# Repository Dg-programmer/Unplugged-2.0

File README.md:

# Unplugged-2.0
Round 2 Codes &amp; Snippets

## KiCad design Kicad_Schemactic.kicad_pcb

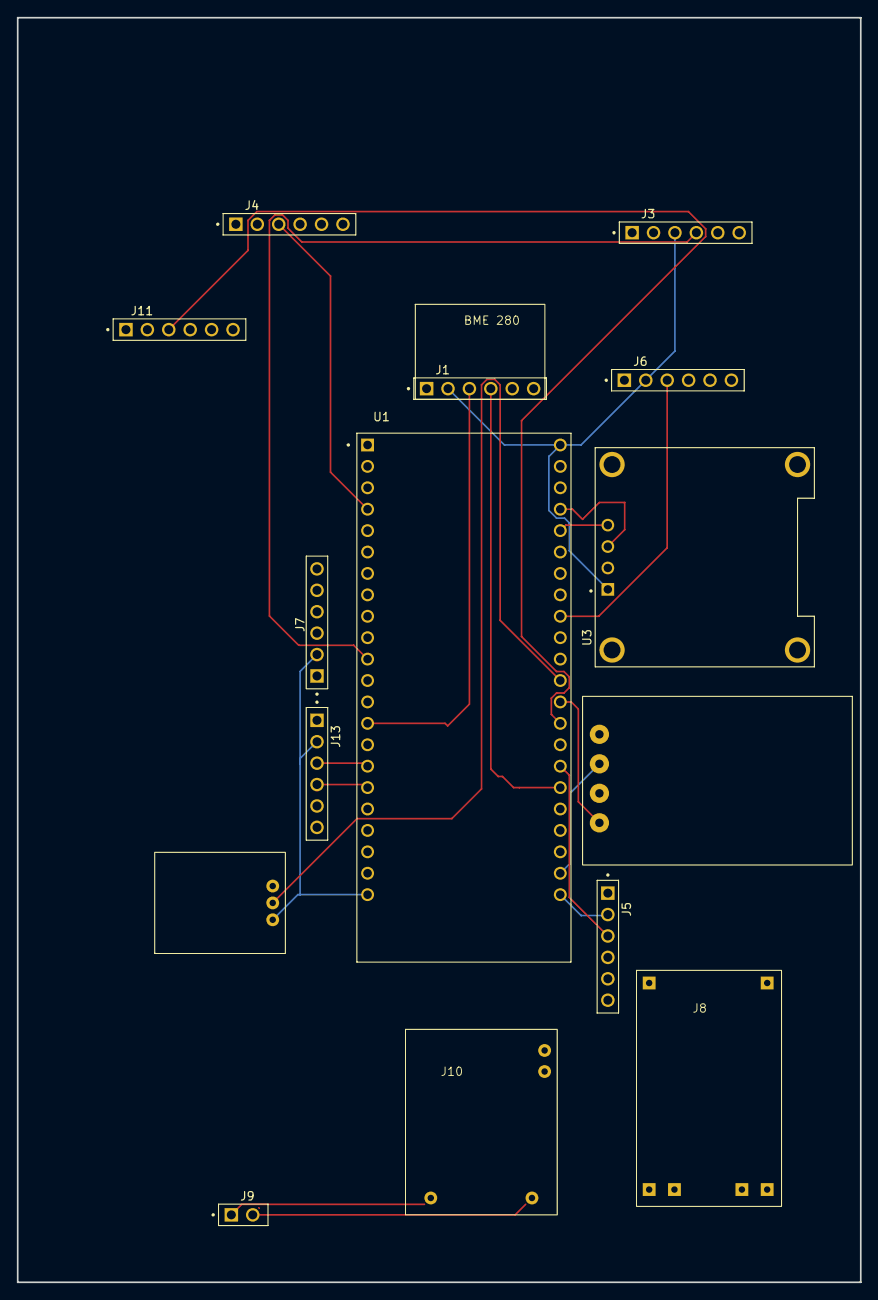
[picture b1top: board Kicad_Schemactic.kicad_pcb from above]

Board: 2 copper layers, 100.0 x 150.0 mm, 15 parts (0 on the bottom side), 16 nets.

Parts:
J1: BME 280; SULLINS_PPTC061LFBN-RC
J2: MQ 135; MQ 185
J3: PMY 2.5; SULLINS_PPTC061LFBN-RC
J4: water sensor; SULLINS_PPTC061LFBN-RC
J5, J7: IR sensor; SULLINS_PPTC061LFBN-RC
J6: Sound Sensor; SULLINS_PPTC061LFBN-RC
J8: Tp4056; TP4056
J9: Battery; SULLINS_PPTC061LFBN-RC
J10: BOOST; Boost
J11: Hall effect; SULLINS_PPTC061LFBN-RC
J12: DHT11
J13: RTC; SULLINS_PPTC061LFBN-RC
U1: ESP32-S3-DEVKITC-1U-N8R2; XCVR_ESP32-S3-DEVKITC-1U-N8R2
U3: Oled display; MODULE_DM-OLED096-636

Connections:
3v: J1.1 (VCC), J2.1 (VCC), U1.J1_1 (3V3), U1.J1_2 (3V3)
5v: J3.1 (VCC), J3.2, J4.1 (VCC), J5.1 (VCC), J6.1 (VCC), J7.1 (VCC), J11.1 (VCC), J12.3 (VCC), J13.1 (VCC), U1.J1_5 (GPIO5), U1.J1_21 (5V0), U3.2 (VCC_IN)
GND: J1.2 (GND), J2.2 (GND), J3.3, J3.5, J4.2 (GND), J5.2 (GND), J6.2 (GND), J7.2 (GND), J11.2 (GND), J12.1 (GND), J13.2 (GND), U1.J1_22 (GND), U1.J3_1 (GND), U1.J3_21 (GND), U1.J3_22 (GND), U3.1 (GND)
unnamed: J1.4 (MOSI), U1.J3_17 (GPIO47)
unnamed: J1.3 (SCK), U1.J1_14 (GPIO46)
unnamed: J2.4 (AO), U1.J3_13 (GPIO35)
unnamed: J4.3 (D0), U1.J1_4 (GPIO4)
unnamed: J5.3 (OUT), U1.J3_16 (GPIO48)
unnamed: J6.3 (D0), U1.J3_9 (MTCK/GPIO39)
unnamed: J11.3 (OUT), U1.J3_14 (GPIO0)
unnamed: J12.2 (DATA), U1.J3_12 (GPIO36)
unnamed: J13.3 (CLK), U1.J1_16 (GPIO10)
unnamed: J13.4 (DAT), U1.J1_17 (GPIO11)
unnamed: U1.J3_4 (GPIO1), U3.3 (SCL)
unnamed: U1.J3_5 (GPIO2), U3.4 (SDA)
unnamed: J3.4, U1.J1_11 (GPIO18)

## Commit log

2025-03-08 Add files via upload
    Schematic
2025-03-08 Add files via upload
    sd
2025-03-08 Add files via upload
    drc
2025-03-08 Add files via upload
    sda
